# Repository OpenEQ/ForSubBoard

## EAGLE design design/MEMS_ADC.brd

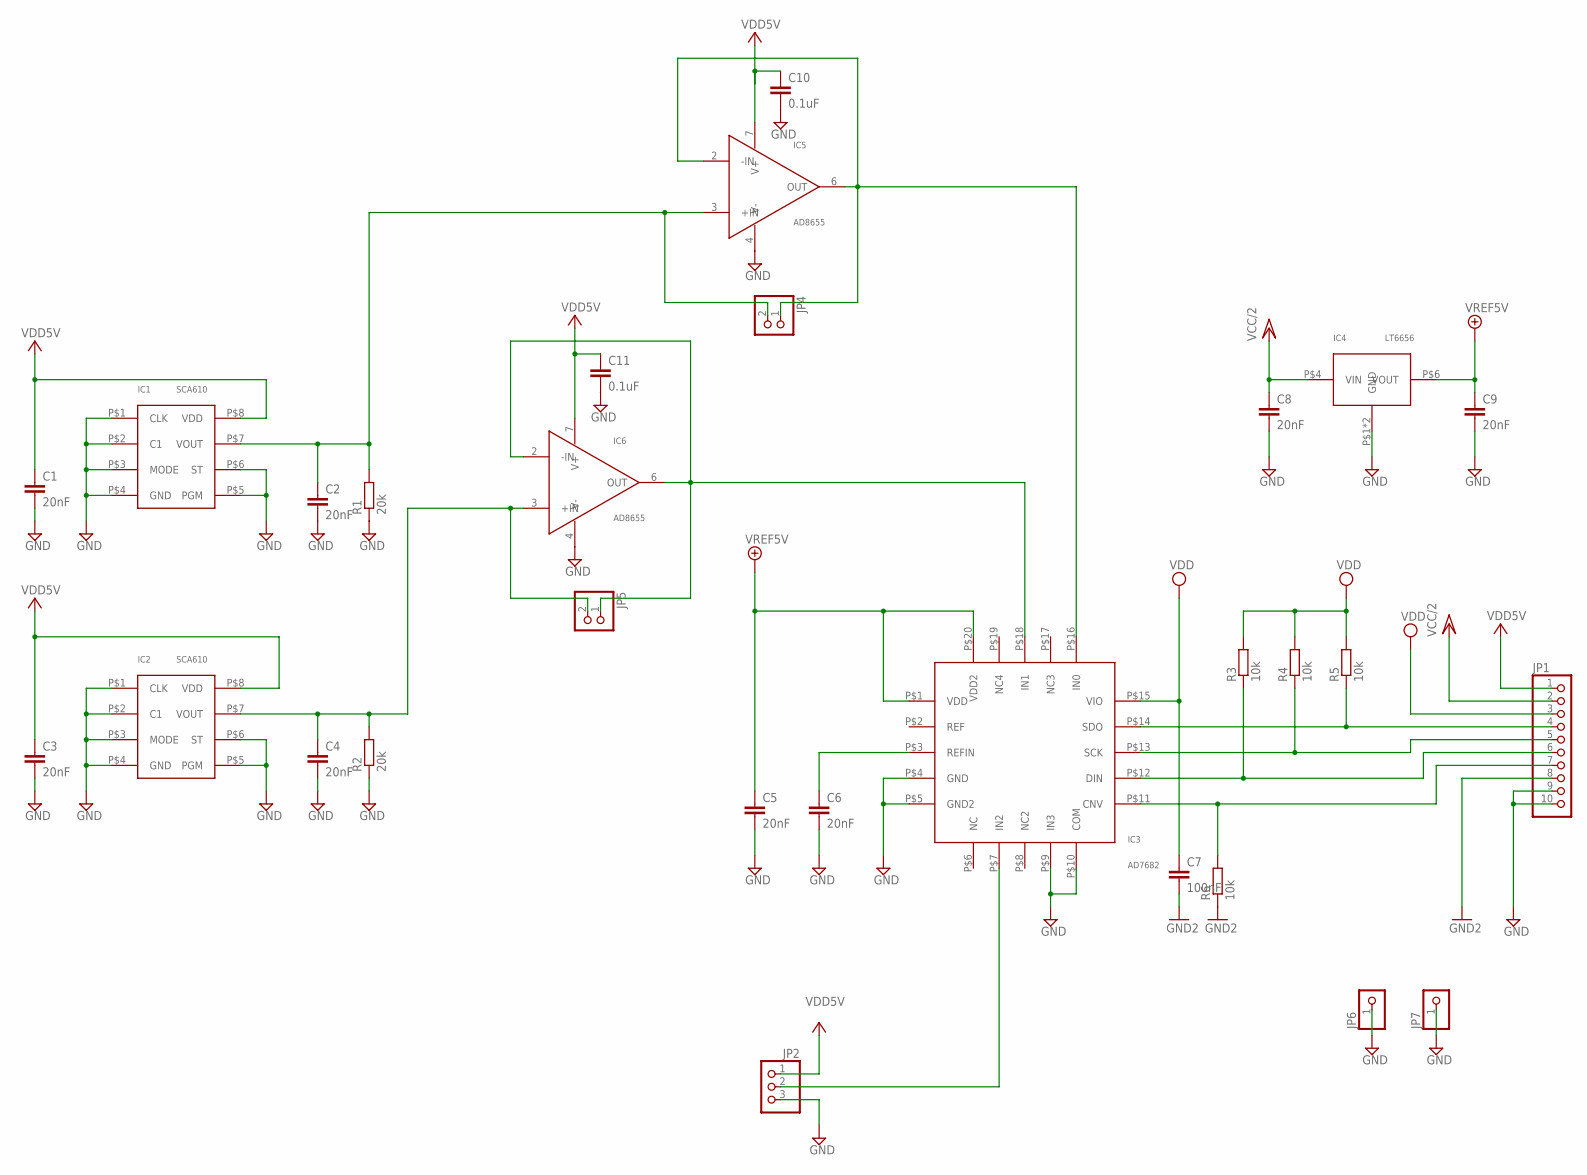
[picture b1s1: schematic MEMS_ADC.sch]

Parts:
C1, C2, C3, C4, C5, C6, C8, C9: 20nF; C0805
C7: 100nF; C0805
C10, C11: 0.1uF; C0805
IC1, IC2: SCA610; SCA610-D14H1
IC3: AD7682
IC4: LT6656; SOT23-6
IC5, IC6: AD8655; SOIC8
JP1: PINHD-1X10; 1X10
JP2: PINHD-1X3; 1X03
JP4, JP5: PINHD-1X2; 1X02
JP6, JP7: PINHD-1X1; 1X01
R1, R2: 20k; R0805
R3, R4, R5, R6: 10k; R0805

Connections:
+5V: C5.1, C9.1, IC3.P$1 (VDD), IC3.P$20 (VDD2), IC4.P$6 (VOUT)
GND: C1.2, C2.2, C3.2, C4.2, C5.2, C6.2, C7.2, C8.2, C9.2, C10.2, C11.2, IC1.P$1 (CLK), IC1.P$2 (C1), IC1.P$3 (MODE), IC1.P$4 (GND), IC1.P$5 (PGM), IC1.P$6 (ST), IC2.P$1 (CLK), IC2.P$2 (C1), IC2.P$3 (MODE), IC2.P$4 (GND), IC2.P$5 (PGM), IC2.P$6 (ST), IC3.P$4 (GND), IC3.P$5 (GND2), IC3.P$9 (IN3), IC3.P$10 (COM), IC4.P$1 (GND), IC4.P$2 (GND), IC5.4 (V-), IC6.4 (V-), JP1.8, JP1.9, JP1.10, JP2.3, JP6.1, JP7.1, R1.1, R2.1, R6.1
unnamed: C4.1, IC2.P$7 (VOUT), IC6.3 (+IN), JP5.2, R2.2
unnamed: IC3.P$11 (CNV), JP1.7, R6.2
unnamed: C6.1, IC3.P$3 (REFIN)
unnamed: IC3.P$12 (DIN), JP1.6, R3.1
unnamed: IC3.P$13 (SCK), JP1.5, R4.1
unnamed: IC3.P$14 (SDO), JP1.4, R5.1
unnamed: C2.1, IC1.P$7 (VOUT), IC5.3 (+IN), JP4.2, R1.2
unnamed: IC3.P$7 (IN2), JP2.2
unnamed: IC3.P$16 (IN0), IC5.2 (-IN), IC5.6 (OUT), JP4.1
unnamed: IC3.P$18 (IN1), IC6.2 (-IN), IC6.6 (OUT), JP5.1
VCC: C1.1, C3.1, C10.1, C11.1, IC1.P$8 (VDD), IC2.P$8 (VDD), IC5.7 (V+), IC6.7 (V+), JP1.1, JP2.1
VCC/2: C8.1, IC4.P$4 (VIN), JP1.2
VDD: C7.1, IC3.P$15 (VIO), JP1.3, R3.2, R4.2, R5.2

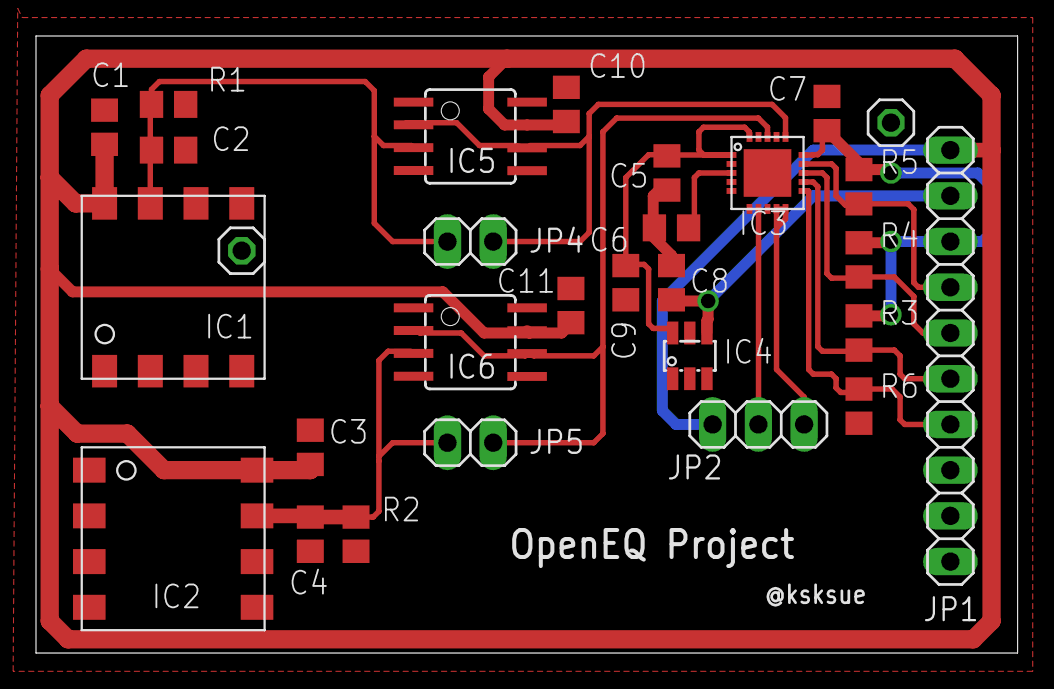
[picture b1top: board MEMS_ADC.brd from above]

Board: 2 copper layers, 54.5 x 34.3 mm, 29 parts (0 on the bottom side), 15 nets.

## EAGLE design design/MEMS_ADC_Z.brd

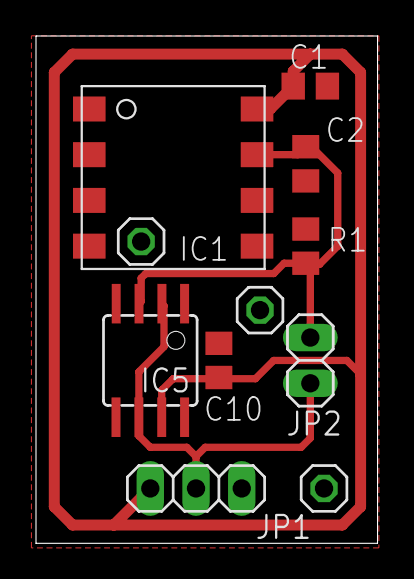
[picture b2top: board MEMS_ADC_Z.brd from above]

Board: 2 copper layers, 19.0 x 28.2 mm, 11 parts (0 on the bottom side), 4 nets.

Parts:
C1, C2: 20nF; C0805
C10: 0.1uF; C0805
IC1: SCA610; SCA610-D14H1
IC5: AD8655; SOIC8
JP1: 1X03
JP2: 1X02
JP3, JP4, JP5: 1X01
R1: 20k; R0805

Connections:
GND: C1.2, C2.2, C10.2, IC1.P$1, IC1.P$2, IC1.P$3, IC1.P$4, IC1.P$5, IC1.P$6, IC5.4, JP1.3, JP3.1, JP4.1, JP5.1, R1.1
unnamed: C2.1, IC1.P$7, IC5.3, JP2.2, R1.2
unnamed: IC5.2, IC5.6, JP1.2, JP2.1
VCC: C1.1, C10.1, IC1.P$8, IC5.7, JP1.1
